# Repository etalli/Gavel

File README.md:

# Gavel

[日本語](README.ja.md)

A physical controller for [Claude Code](https://claude.ai/code). · [Landing page](https://etalli.github.io/Gavel/)

**Why "Gavel"?** A judge's gavel makes decisions final — and here, the human is always the judge. Any keyboard could send the same keys, but a dedicated device makes you stop and think instead of pressing keys on autopilot. A ruling, not a reflex.
Gavel acts as a physical reminder and a friction layer against autopilot mode: pause, think, then decide.
Happy coding!
---

## What it does

- **Input** — Three physical buttons answer Claude Code's permission prompts (`1` Allow Once / `2` Always Allow / `3` Reject) without touching the keyboard.
- **Output** — LEDs light up in response to Claude Code hook events, giving real-time feedback on what Claude is doing. Color and pattern vary by tool risk category (read / write / network / destructive).
- **Log** — Every button press is appended to `~/.claude/gavel/decisions.jsonl` for decision history. Run `python3 hooks/stats.py` to see a summary.

---

## Hardware

The PCB is designed for the **Waveshare RP2040 Zero**.

| Board | LED output | Status |
|-------|-----------|--------|
| Waveshare RP2040 Zero | RGB NeoPixel (GP16) + 3× button LEDs (GP2/GP3/GP4) | Primary (PCB supported) |
| Raspberry Pi Pico | 3× discrete LEDs (GP2/GP3/GP4) | Legacy / DIY wiring only |

The NeoPixel shows the tool risk category color. The 3 button LEDs (one per switch) light up to confirm which button was pressed.

Board type is auto-detected — no manual configuration needed.

Both use the same GPIO pins for buttons (GP14/GP15/GP26). See [`hardware/wiring.md`](hardware/wiring.md) for full pin assignments.

---

## How it works

The microcontroller runs two independent roles over a single USB cable:

1. **USB HID keyboard** — pressing a button sends the matching keypress to the terminal. Claude Code receives it exactly as if the user typed it. No special Claude Code configuration needed.

2. **Serial listener** — Claude Code hooks call Python scripts on the Mac side, which send small JSON messages over the microcontroller's USB serial port to control the LEDs.

| Hook | Category | NeoPixel | Discrete LEDs |
|---|---|---|---|
| `PreToolUse` | readonly (Read / Grep / LS) | Blue | Center LED dim |
| `PreToolUse` | write (Edit / Write) | Yellow | Two LEDs dim |
| `PreToolUse` | network (WebFetch / Agent) | Orange blink | Blink |
| `PreToolUse` | destructive (Bash etc.) | Red | All bright |
| `PostToolUse` | — | Off | Off |
| `Notification` (info) | — | Single slow flash | Single slow flash |
| `Notification` (warn) | — | Three medium flashes | Three medium flashes |
| `Notification` (error) | — | Five fast red flashes | Five fast flashes |
| `PostToolUse` (context ≥ 90%) | — | Three medium flashes, then off | Three medium flashes, then off |

---

## Setup

### 1. Hardware Firmware
1. Install [CircuitPython](https://circuitpython.org) on your board
2. Download the [CircuitPython library bundle](https://circuitpython.org/libraries) matching your CircuitPython version
3. Copy the following to `CIRCUITPY/lib/`:
   - `adafruit_hid/` (folder) — required for all boards
   - `neopixel.mpy` — required for Waveshare RP2040 Zero only
4. Copy `firmware/boot.py` and `firmware/code.py` to the `CIRCUITPY` drive  
   *(Alternatively, run `./install.sh` to automate this step)*
5. **Power cycle** the board (unplug and replug USB) so `boot.py` takes effect
6. Wire buttons and LEDs per [`hardware/wiring.md`](hardware/wiring.md)

### 2. Software (Claude Code Hooks)
1. Install the Mac-side dependency: `pip3 install pyserial`
2. Add the project's hook scripts to your `~/.claude/settings.json` (instructions pending).
3. **Optional:** Run `./install.sh --deploy` to copy the hook scripts to a stable location (`~/.claude/gavel/`) and automatically update their paths in `settings.json`. This is recommended if you plan to move or rename the project folder.

---

## Troubleshooting

**LEDs do not respond when running hook scripts manually from the terminal**

```
No module named 'serial'
```

`pyserial` may not be installed for the `python3` used in your terminal session. Fix with:

```bash
pip3 install pyserial
```

Note: Claude Code hooks may use a different Python environment that already has `pyserial` installed, so hooks can work in a Claude Code session even when manual terminal tests fail.

---

## License

MIT License — see [LICENSE](LICENSE) for details.

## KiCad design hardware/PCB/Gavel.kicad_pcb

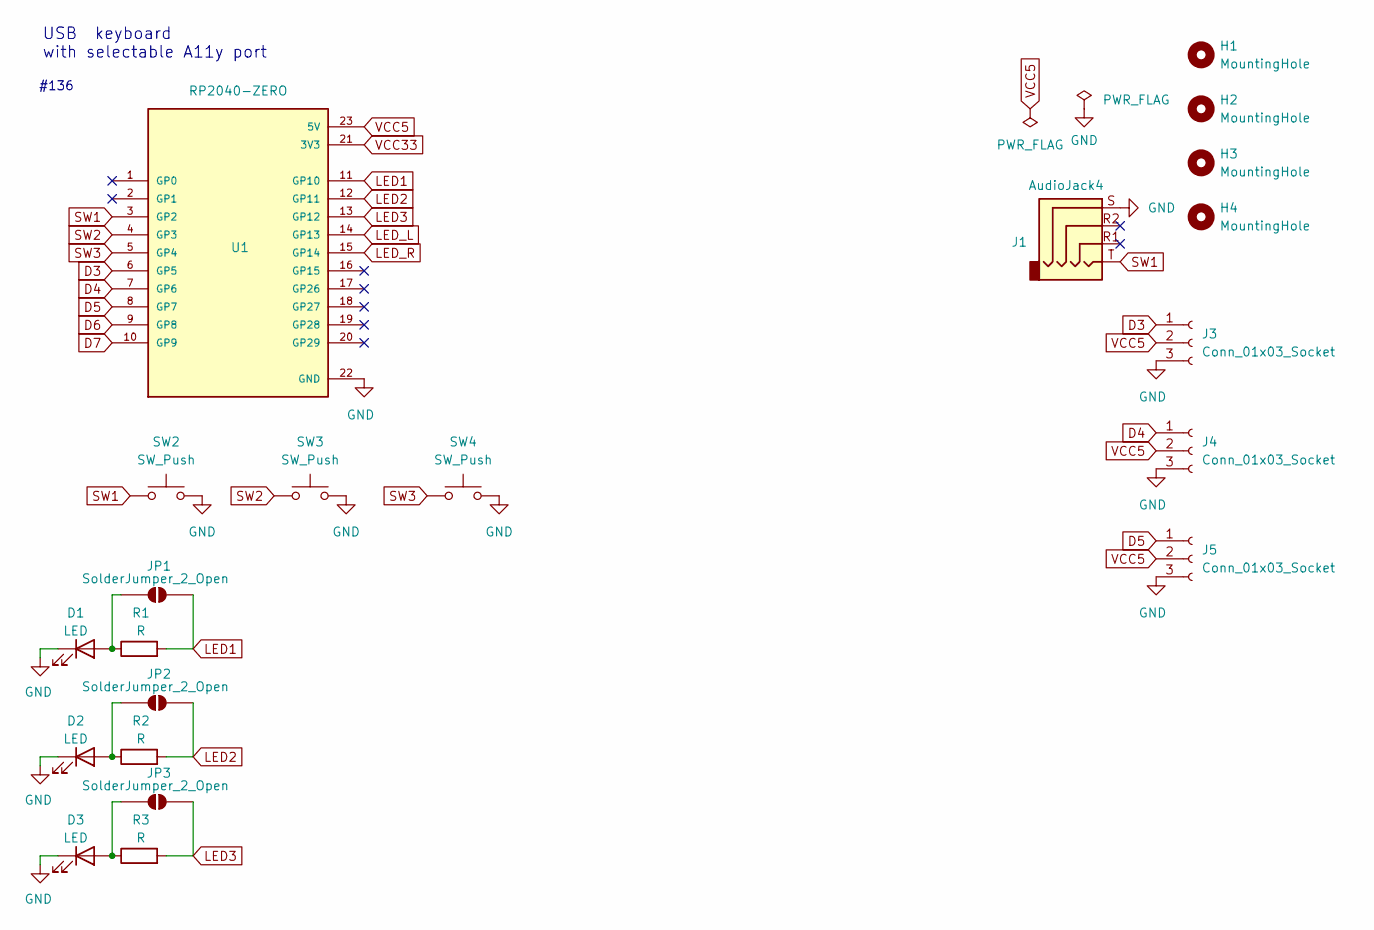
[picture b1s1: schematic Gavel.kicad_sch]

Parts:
D1, D2, D3: LED; LED_D3.0mm
H1, H2, H3, H4: MountingHole; MountingHole_2.2mm_M2
J1: AudioJack4; MJ-4PP-9_1side
J3, J4, J5: Conn_01x03_Socket; JST_PH_S3B-PH-K_1x03_P2.00mm_Horizontal
JP1, JP2, JP3: SolderJumper_2_Open; SolderJumper-2_P1.3mm_Open_RoundedPad1.0x1.5mm
R1, R2, R3: R; R_Axial_DIN0204_L3.6mm_D1.6mm_P7.62mm_Horizontal
SW2, SW3, SW4: SW_Push; k2_CherryMX_KailhChocV1_Socket_Diode-rev2
U1: RP2040-ZERO; MODULE_RP2040-ZERO; PARTREV NA

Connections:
D3: J3.1, U1.6 (GP5)
D4: J4.1, U1.7 (GP6)
D5: J5.1, U1.8 (GP7)
D6: U1.9 (GP8)
D7: U1.10 (GP9)
GND: D1.1 (K), D2.1 (K), D3.1 (K), J1.S, J3.3, J4.3, J5.3, SW2.2, SW3.2, SW4.2, U1.22 (GND)
LED1: JP1.2 (B), R1.2, U1.11 (GP10)
LED2: JP2.2 (B), R2.2, U1.12 (GP11)
LED3: JP3.2 (B), R3.2, U1.13 (GP12)
LED_L: U1.14 (GP13)
LED_R: U1.15 (GP14)
unnamed: D1.2 (A), JP1.1 (A), R1.1
unnamed: D2.2 (A), JP2.1 (A), R2.1
unnamed: D3.2 (A), JP3.1 (A), R3.1
SW1: J1.T, SW2.1, U1.3 (GP2)
SW2: SW3.1, U1.4 (GP3)
SW3: SW4.1, U1.5 (GP4)
VCC5: J3.2, J4.2, J5.2, U1.23 (5V)
VCC33: U1.21 (3V3)

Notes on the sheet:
USB keyboard with selectable A11y port
#136

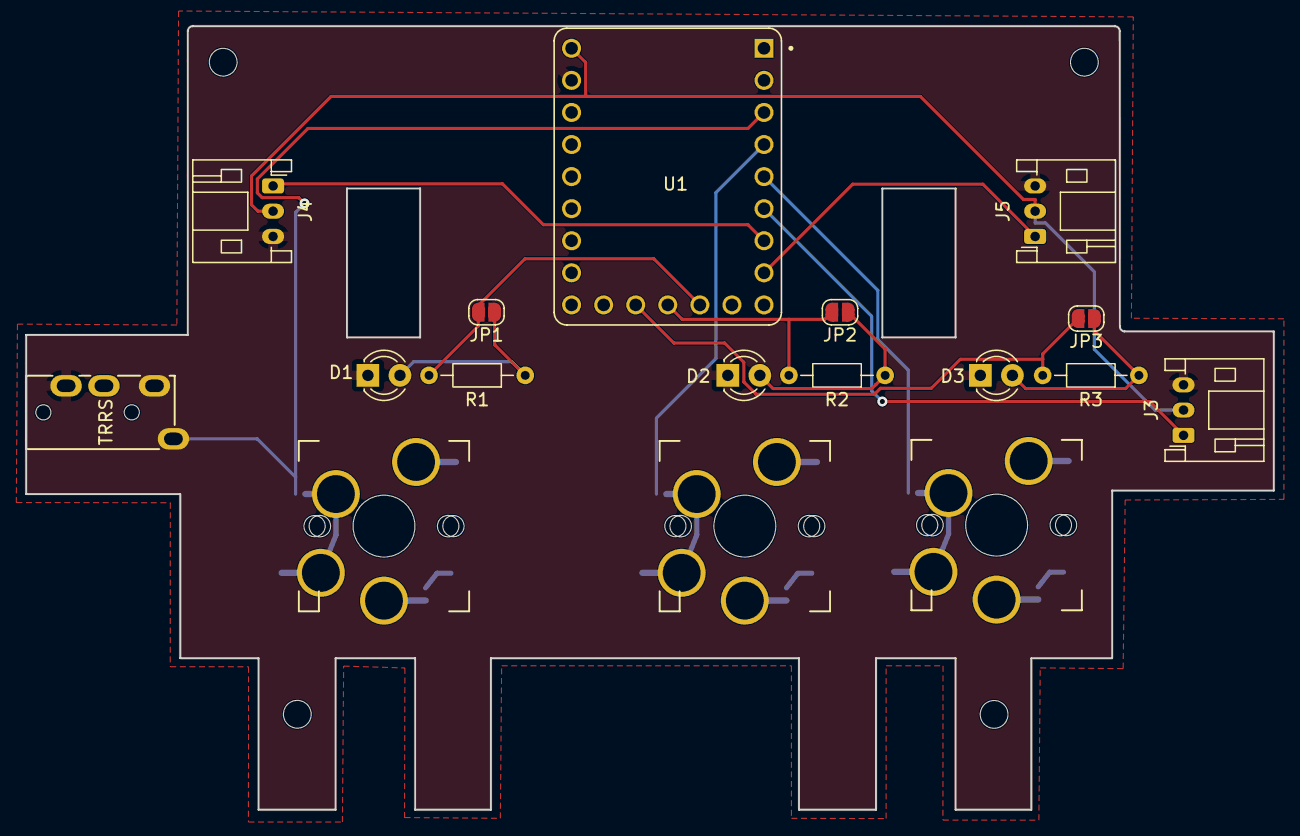
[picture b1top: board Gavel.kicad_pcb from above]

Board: 2 copper layers, 98.8 x 62.1 mm, 21 parts (0 on the bottom side), 14 nets.

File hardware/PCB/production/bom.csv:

Designator,Footprint,Quantity,Value,LCSC Part #
"D1, D2, D3",LED_D3.0mm,3,LED,
"H1, H2, H3, H4",MountingHole_2.2mm_M2,4,MountingHole,
J1,MJ-4PP-9_1side,1,AudioJack4,
"J3, J4, J5",JST_PH_S3B-PH-K_1x03_P2.00mm_Horizontal,3,Conn_01x03_Socket,
"R1, R2, R3",R_Axial_DIN0204_L3.6mm_D1.6mm_P7.62mm_Horizontal,3,R,
"SW2, SW3, SW4",k2_CherryMX_KailhChocV1_Socket_Diode-rev2,3,SW_Push,
U1,MODULE_RP2040-ZERO,1,RP2040-ZERO,

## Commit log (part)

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2026-04-11 Add SVG icon and installation script for Gavel firmware
    - Created a new SVG file for the Gavel icon with a rounded rectangle background and gavel design.
    - Added an installation script (install.sh) to automate the firmware installation process on the Raspberry Pi Pico, ensuring compatibility with the CIRCUITPY drive.
2026-04-11 Move assets and docs into docs/ folder; add README.md
2026-04-11 Remove Pico-specific references in README; use generic terms
2026-04-12 Add LED test script and update permissions for CIRCUITPY access
2026-04-12 Refactor hooks: extract shared pico.py, fix post_tool idle payload
2026-04-12 Fix misleading comment in find_device.py about data port suffix
2026-04-12 Log serial exceptions to hook.log instead of swallowing silently
2026-04-12 Add --deploy option to install.sh: copies hooks to ~/.claude/gavel/
2026-04-12 Move serial import inside try block to avoid ImportError when pyserial missing
2026-04-12 Log errors only: skip routine tool call logging to prevent hook.log bloat
2026-04-12 Remove Enter keypress from button actions for VS Code extension compatibility
2026-04-12 Remove CCKN references; update Architecture.md folder name to Gavel
2026-04-12 fix: send 1/2/3 keycodes instead of y/a/n for VS Code Claude Code compatibility
2026-04-12 docs: update README — 1/2/3 keycodes, add --deploy option
2026-04-13 Add reset button wiring: RUN pin to GND
2026-04-13 fix: remove unused press_enter() function from firmware (Close #8)
2026-04-13 fix: remove misleading BAUD_RATE constant in pico.py (Close #6)
2026-04-13 Add project landing page with GitHub link and install instructions
2026-04-13 Update Why Gavel description on landing page
2026-04-13 docs: add troubleshooting tip for missing pyserial in terminal
2026-04-13 fix: auto-install pyserial in install.sh --deploy if missing
2026-04-13 docs: add wiring guide link and releases link to landing page
2026-04-13 feat: add implementation plan for physical feedback mechanism and related documentation updates
2026-04-13 Add ROADMAP.md with three-phase feature plan
2026-04-13 Remove implementation_plan.md; superseded by ROADMAP.md
2026-04-13 Update Architecture.md: fix keycodes, file layout, reset button, install steps
2026-04-13 Move PNG icons to docs/images/; update references in README, index.html, Architecture.md
2026-04-13 Move icon.svg to docs/images/; update Architecture.md
2026-04-13 Add Stop hook to turn off LEDs on session end
2026-04-13 Document Stop hook in Architecture.md
2026-04-14 feat: night rider idle animation on LEDs (Close #11)
2026-04-14 feat: toggle KITT animation with Button 2 + Button 3 combo (Close #12)
2026-04-14 fix: reliable combo detection for KITT toggle (40ms window)
2026-04-14 feat: KITT animation default off
2026-04-14 Add KITT animation demo to landing page table
2026-04-14 feat: NeoPixel mode for Waveshare RP2040 Zero with breathing animation (Close #2)
2026-04-14 refactor: gather config constants at top of code.py
2026-04-14 feat: NeoPixel blue sine breathing animation for RP2040 Zero
2026-04-14 docs: update README with CircuitPython library requirements and power cycle note
2026-04-16 fix: auto-return to idle after 5s permission timeout (Close #14)
2026-04-16 fix: set USE_NEOPIXEL=False for Pico
2026-04-16 feat: auto-detect board via board.board_id (Close #13)
2026-04-16 refactor: move KITT_DEFAULT to config block at top of code.py
2026-04-16 chore: ignore *.zip and *.webloc files
2026-04-16 docs: update Architecture.md and add behavior.md firmware reference
2026-04-18 refactor: rename t to msg_type in serial handler (Close #23)
2026-04-18 refactor: extract notification flash logic into flash_for_level() (Close #22)
2026-04-18 feat: warn via LED when context window usage reaches 90%
2026-04-18 debug: log PostToolUse payload to verify context_window_utilization
2026-04-24 docs: add neopixel.mpy to firmware requirements for RP2040 Zero
2026-04-24 feat: drive both NeoPixel and discrete LEDs simultaneously on RP2040 Zero
2026-04-24 fix: invert discrete LED polarity for active-low wiring on RP2040 Zero PCB
2026-04-24 chore: release prep — gitignore log files, fix auto-detect docs, add TEST.md
    - .gitignore: broaden hooks/hook.log to hooks/*.log to cover debug payload logs
    - README.md, hardware/wiring.md: remove manual USE_NEOPIXEL config column; board type is auto-detected
    - docs/TEST.md: fix misleading instruction to manually set USE_NEOPIXEL
    - docs/TEST.md: add hardware kit test checklist
2026-04-24 fix: use active-high polarity for discrete LEDs on all boards
2026-04-24 docs: add RP2040 Zero discrete LED wiring to wiring.md
2026-04-24 refactor: collapse button handlers into BUTTONS table (Close #21)
2026-04-24 docs: update GPIO pin assignments to match firmware (buttons GP14/15/26, LEDs GP2/3/4)
2026-04-24 fix: update test_leds.py GPIO pins to match firmware (GP2/3/4)
2026-04-25 docs: sync all docs to latest code
2026-04-25 docs: add landing page link to README
2026-04-25 docs: add Japanese landing page with language switcher
2026-04-25 docs: add language switcher at top of landing pages
2026-04-25 docs: update footer text for clarity in Japanese landing page
2026-04-25 docs: improve Why Gavel section in README (EN + JA)
2026-04-25 docs: add Happy coding! to Why Gavel section
2026-04-25 feat: hold decision LED for 2s after button press (fix #9)
2026-04-25 feat: hold decision LED for 2s after button press (#25)
    * docs: improve Why Gavel section in README (EN + JA)
    * docs: add Happy coding! to Why Gavel section
    * feat: hold decision LED for 2s after button press (fix #9)
2026-04-25 fix: move decision_off_at out of press_button to fix button detection during permission state
2026-04-25 fix: raise DEBOUNCE_MS to 300 to prevent chattering after fast press_button return
2026-04-25 fix: require button release before next press to eliminate chattering
2026-04-25 feat: B1+B2 combo sends Cmd+T to toggle extended thinking (Close #15)
2026-04-25 feat: LED patterns per tool category in PreToolUse (Close #4)
2026-04-25 feat: LED patterns per tool category in PreToolUse (Close #4) (#28)
2026-04-25 feat: tool-specific NeoPixel colors per risk category (Close #17)
    readonly → blue, write → yellow (two LEDs dim), destructive → red.
    Adds WRITE_TOOLS set (Edit/Write/MultiEdit/NotebookEdit) to pre_tool.py
    so file-modifying tools show yellow instead of full-alert red.
2026-04-25 feat: add test_leds.py to manually verify all LED patterns
2026-04-25 feat: tool-specific NeoPixel colors per risk category (#30)
    * feat: tool-specific NeoPixel colors per risk category (Close #17)
    readonly → blue, write → yellow (two LEDs dim), destructive → red.
    Adds WRITE_TOOLS set (Edit/Write/MultiEdit/NotebookEdit) to pre_tool.py
    so file-modifying tools show yellow instead of full-alert red.
    * feat: add test_leds.py to manually verify all LED patterns
2026-04-25 feat: log button decisions from Pico to Mac (Close #5)
    Pico writes {"event":"button","button":"allow_once|always_allow|reject"}
    to serial on each press. The next hook call drains the buffer and appends
    timestamped events to ~/.claude/gavel/decisions.jsonl.
2026-04-25 feat: log button decisions from Pico to Mac (Close #5) (#29)
    Pico writes {"event":"button","button":"allow_once|always_allow|reject"}
    to serial on each press. The next hook call drains the buffer and appends
    timestamped events to ~/.claude/gavel/decisions.jsonl.
2026-04-25 docs: update README with LED color categories and decision log
2026-04-25 docs: sync README.ja.md with LED color categories and decision log
2026-04-26 feat: remove permission timeout — LEDs stay lit until button pressed (Close #32)
2026-04-26 docs: RP2040 Zero is primary board, Pico noted as legacy
2026-04-26 docs: PCB has NeoPixel + 3 button LEDs, clarify each LED's role
2026-04-26 docs: update Architecture.md — LED categories, button LEDs, decision log, no timeout
2026-04-26 feat: add test_decisions.py for decision logging e2e test (Close #33)
2026-04-26 fix: buffer button events when serial port closed, flush on reconnect (Close #34)
2026-04-26 fix: flush button queue on message receipt; add 200ms read delay in pico.py
2026-04-26 fix: always queue button events, flush on next message receipt
2026-04-26 another one
2026-04-26 ORDERED JLCPCB
2026-04-26 Update .gitignore
    Delete ~Gavel-TopPlate.kicad_pro.lck
    a
2026-04-29 feat: add stats.py CLI for decision log summary (Close #19)
2026-04-29 docs: mention stats.py in README
2026-04-30 feat: add vibration motor support on GP5
    - buzz() helper: configurable pulses (times, on_ms, off_ms)
    - 2 pulses on permission request (alert)
    - 1 pulse on button press (confirmation)
    - 3 pulses on error notification
2026-04-30 test: add vibration motor test script (GP5)
2026-04-30 docs: add devlog entry for 2026-05-01 Codex review (issue #36)
2026-05-01 docs: correct devlog — issue #36 was false alarm (SVG is laser-cut file)
2026-05-02 feat: servo angle encodes notification severity on GP6 (Close #37)
    - set_servo(angle) helper: maps 0-180° to 1-2ms pulse at 50Hz
    - idle=0°, info=45°, warn=90°, error=135°
    - servo resets to 0° on button press and idle message
    - moved pwmio import to top-level
2026-05-02 test: add servo test script (GP6)
2026-05-02 fix: always write hook.log in send_to_pico, not only on error
2026-05-02 release: v1.0.6 — servo notification indicator
2026-05-02 feat: v3 PCB pin reassignment — buttons GP2/3/4, LEDs GP10/11/12
    v2: buttons GP14/15/26, LEDs GP2/3/4
    v3: buttons GP2/3/4, LEDs GP10/11/12
    Update docstring and production files (BOM, designators, netlist, positions)
2026-05-02 release: v1.0.7 — v3 PCB pin reassignment
2026-05-02 refactor: remove v2 board pin comments, v3 only
2026-05-02 refactor: move pin assignments to config block at top
2026-05-02 refactor: move pin assignments to very top of config block
2026-05-02 feat: long press macro — hold 800ms to type MACROS string (Close #38)
    - KeyboardLayoutUS added for string typing
    - btn_down_idx/btn_down_at state tracks held button non-blocking
    - short press (<800ms) → existing keycode behavior
    - long press (>=800ms) → type_string(MACROS[btn])
    - combo (B2+B3) unchanged — immediate KITT toggle
2026-05-02 chore: update macro strings for each button
2026-05-02 release: v1.0.8 — long press macro
2026-05-02 docs: add devlog entry for 2026-05-03
2026-05-03 test: add external NeoPixel test script (GP0)
2026-05-03 feat: dual NeoPixel eyes on GP0/GP1 mirror built-in NeoPixel (Close #39)
